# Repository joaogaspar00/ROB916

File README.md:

<div style="display: flex; justify-content: center; width: 100%; gap: 250px;">

</div>
<h2 style="text-align: center;">Repositório Material ROB9-16</h2>

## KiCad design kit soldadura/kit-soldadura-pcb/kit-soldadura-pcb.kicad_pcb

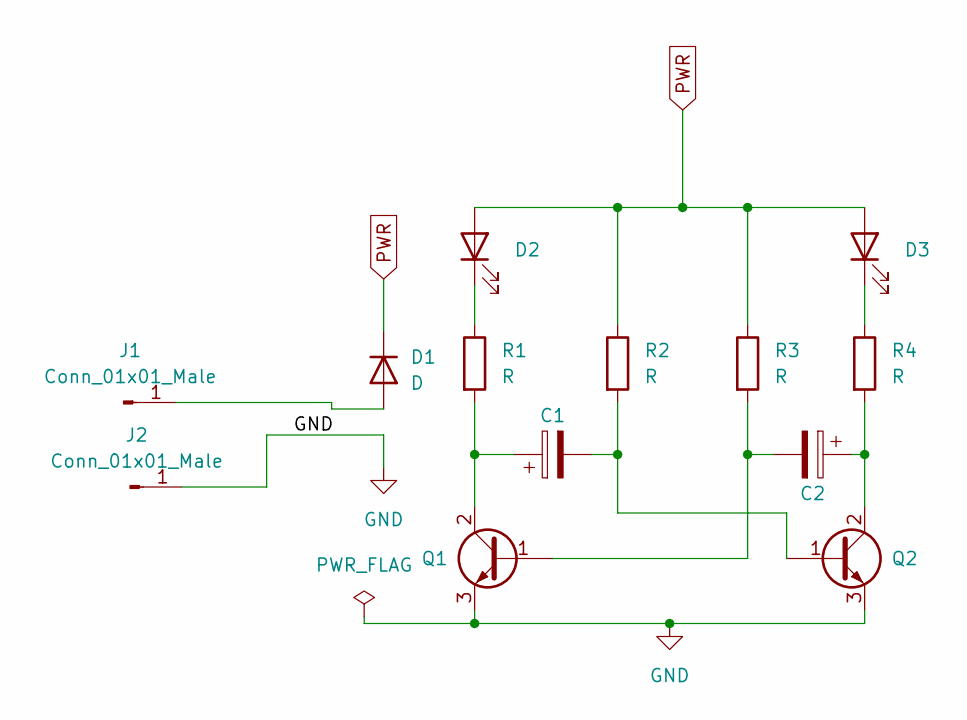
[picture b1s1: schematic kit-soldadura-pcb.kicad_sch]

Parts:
C1, C2: C_Polarized; CP_Radial_D5.0mm_P2.00mm
D1: D; D_5W_P12.70mm_Horizontal
D2, D3: LED; LED_D5.0mm
J1, J2: Conn_01x01_Male; pad
Q1, Q2: Q_NPN_BCE; TO92
R1, R2, R3, R4: R; R_Axial_DIN0309_L9.0mm_D3.2mm_P12.70mm_Horizontal

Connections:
GND: J2.1, Q1.3 (E), Q2.3 (E)
unnamed: C1.1, Q1.2 (C), R1.2
unnamed: C1.2, Q2.1 (B), R2.2
unnamed: C2.1, Q2.2 (C), R4.2
unnamed: C2.2, Q1.1 (B), R3.2
unnamed: D1.2 (A), J1.1
unnamed: D2.1 (K), R1.1
unnamed: D3.1 (K), R4.1
PWR: D1.1 (K), D2.2 (A), D3.2 (A), R2.1, R3.1

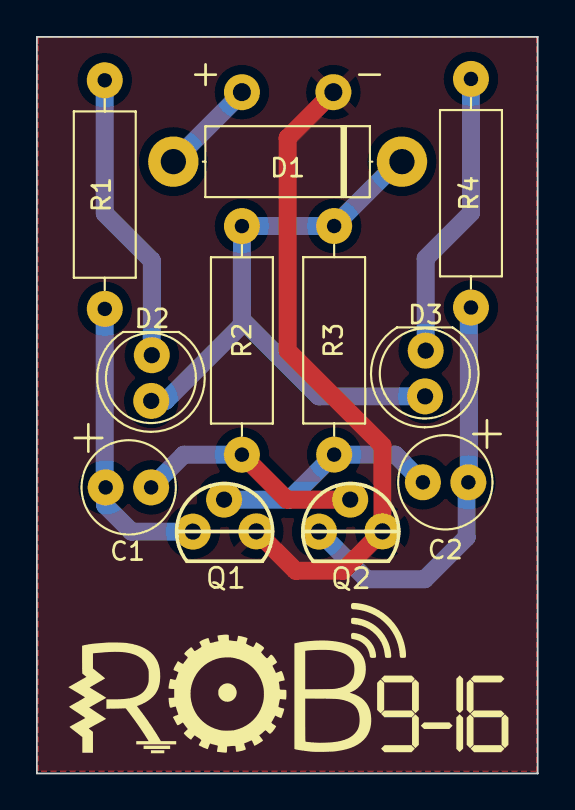
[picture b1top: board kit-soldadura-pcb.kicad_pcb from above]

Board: 2 copper layers, 27.8 x 40.9 mm, 13 parts (0 on the bottom side), 9 nets.

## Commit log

2025-01-17 add activities
